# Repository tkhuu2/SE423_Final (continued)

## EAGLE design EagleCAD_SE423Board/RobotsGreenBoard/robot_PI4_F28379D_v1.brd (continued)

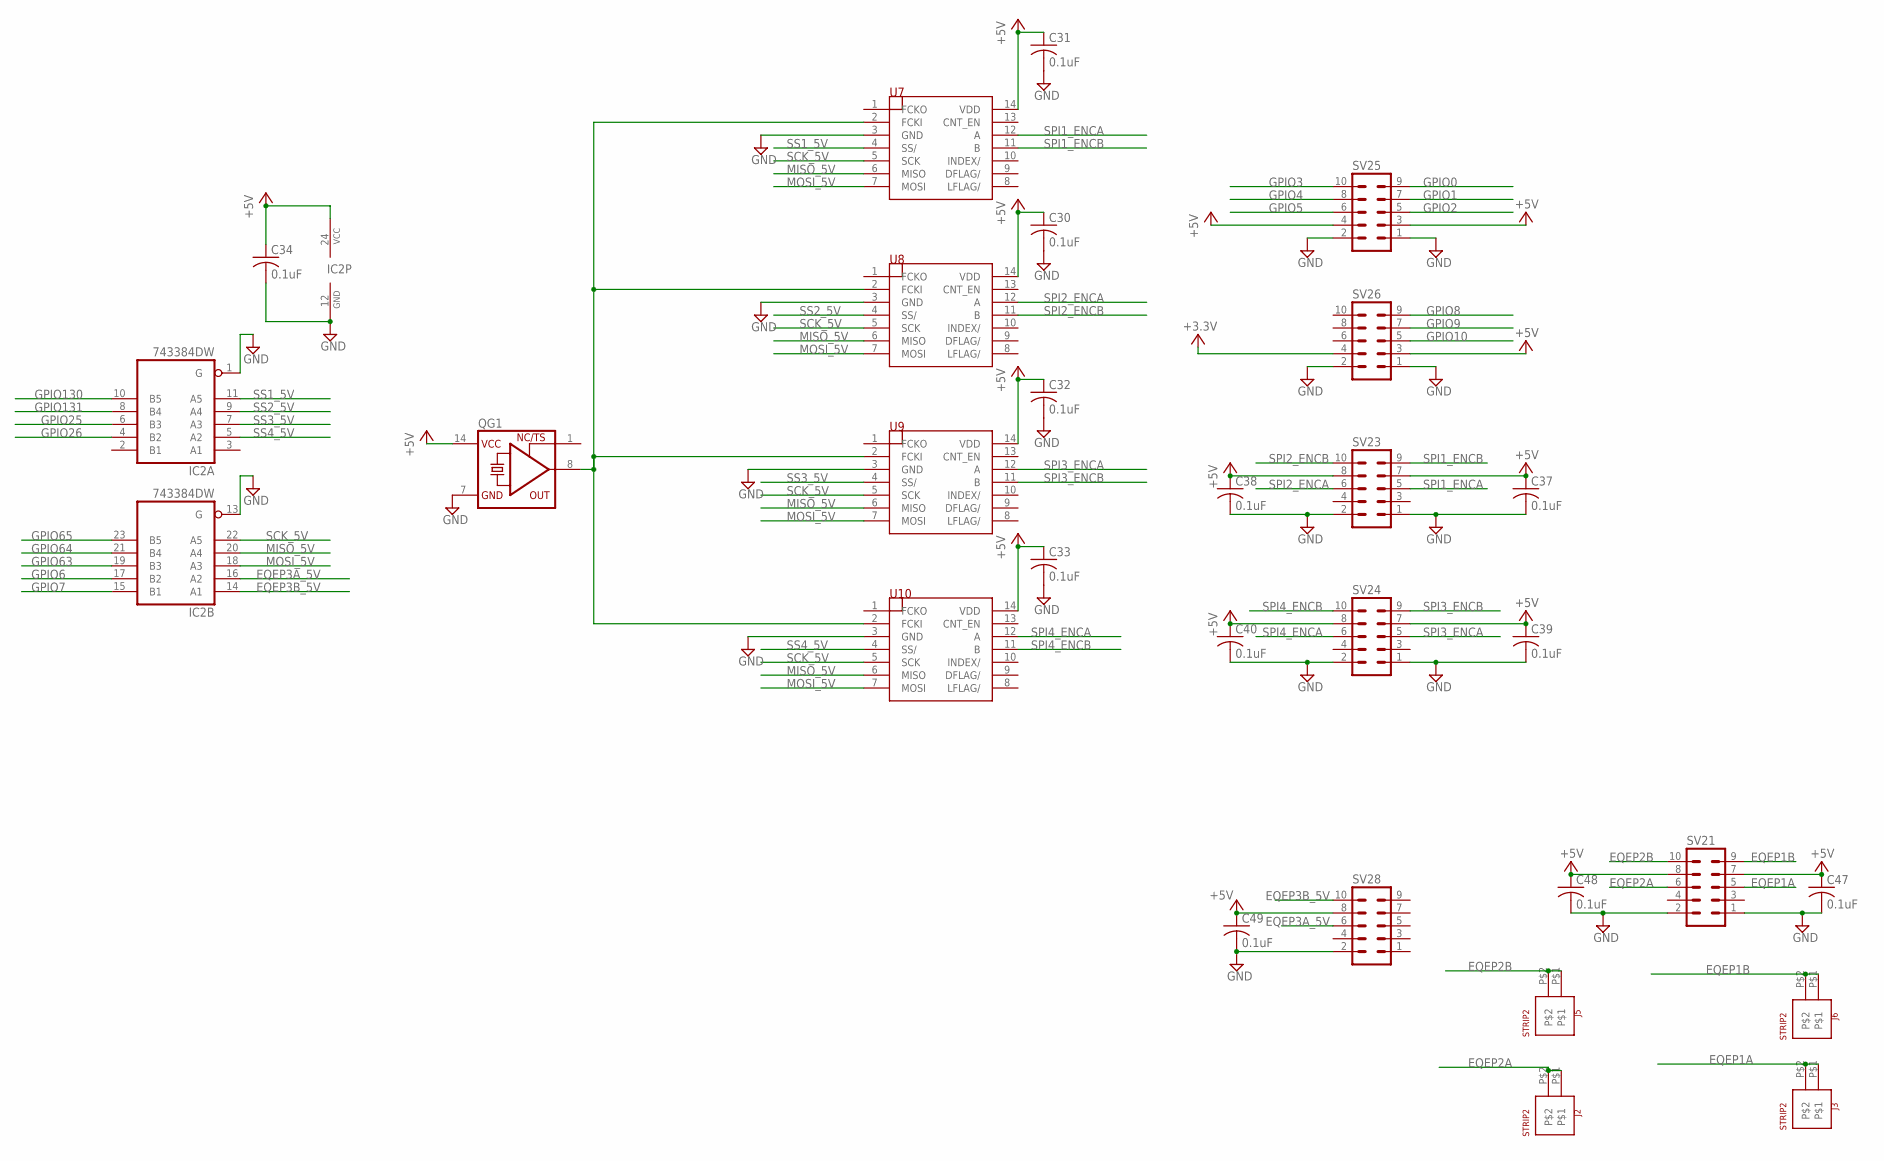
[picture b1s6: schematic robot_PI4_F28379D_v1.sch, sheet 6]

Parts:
C30, C31, C32, C33, C34, C37, C38, C39, C40, C47, C48, C49: 0.1uF; C1206
IC2: 743384DW; SO24W
J2, J3, J5, J6: STRIP2
QG1: XO-14; DIL14S
SV21, SV23, SV24, SV25, SV26, SV28: MA05-2
U7, U8, U9, U10: LS7366R; SO14

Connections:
+3.3V: SV26.4; also elsewhere on the board
+5V: C30.1, C31.1, C32.1, C33.1, C34.1, C37.1, C38.1, C39.1, C40.1, C47.1, C48.1, C49.1, IC2.24 (VCC), QG1.14 (VCC), SV21.7, SV21.8, SV23.7, SV23.8, SV24.7, SV24.8, SV25.3, SV25.4, SV26.3, SV28.8, U7.14 (VDD), U8.14 (VDD), U9.14 (VDD), U10.14 (VDD); also elsewhere on the board
EQEP1A: J3.P$1, J3.P$2, SV21.5
EQEP1B: J6.P$1, J6.P$2, SV21.9
EQEP2A: J2.P$1, J2.P$2, SV21.6
EQEP2B: J5.P$1, J5.P$2, SV21.10
EQEP3A_5V: IC2.16 (A2), SV28.6
EQEP3B_5V: IC2.14 (A1), SV28.10
GND: C30.2, C31.2, C32.2, C33.2, C34.2, C37.2, C38.2, C39.2, C40.2, C47.2, C48.2, C49.2, IC2.1 (G), IC2.12 (GND), IC2.13 (G), QG1.7 (GND), SV21.1, SV21.2, SV23.1, SV23.2, SV24.1, SV24.2, SV25.1, SV25.2, SV26.1, SV26.2, SV28.2, U7.3 (GND), U8.3 (GND), U9.3 (GND), U10.3 (GND); also elsewhere on the board
GPIO0: SV25.9; also elsewhere on the board
GPIO1: SV25.7; also elsewhere on the board
GPIO2: SV25.5; also elsewhere on the board
GPIO3: SV25.10; also elsewhere on the board
GPIO4: SV25.8; also elsewhere on the board
GPIO5: SV25.6; also elsewhere on the board
GPIO6: IC2.17 (B2); also elsewhere on the board
GPIO7: IC2.15 (B1); also elsewhere on the board
GPIO8: SV26.9; also elsewhere on the board
GPIO9: SV26.7; also elsewhere on the board
GPIO10: SV26.5; also elsewhere on the board
GPIO25: IC2.6 (B3); also elsewhere on the board
GPIO26: IC2.4 (B2); also elsewhere on the board
GPIO63: IC2.19 (B3); also elsewhere on the board
GPIO64: IC2.21 (B4); also elsewhere on the board
GPIO65: IC2.23 (B5); also elsewhere on the board
GPIO130: IC2.10 (B5); also elsewhere on the board
GPIO131: IC2.8 (B4); also elsewhere on the board
MISO_5V: IC2.20 (A4), U7.6 (MISO), U8.6 (MISO), U9.6 (MISO), U10.6 (MISO)
MOSI_5V: IC2.18 (A3), U7.7 (MOSI), U8.7 (MOSI), U9.7 (MOSI), U10.7 (MOSI)
unnamed: QG1.8 (OUT), U7.2 (FCKI), U8.2 (FCKI), U9.2 (FCKI), U10.2 (FCKI)
SCK_5V: IC2.22 (A5), U7.5 (SCK), U8.5 (SCK), U9.5 (SCK), U10.5 (SCK)
SPI1_ENCA: SV23.5, U7.12 (A)
SPI1_ENCB: SV23.9, U7.11 (B)
SPI2_ENCA: SV23.6, U8.12 (A)
SPI2_ENCB: SV23.10, U8.11 (B)
SPI3_ENCA: SV24.5, U9.12 (A)
SPI3_ENCB: SV24.9, U9.11 (B)
SPI4_ENCA: SV24.6, U10.12 (A)
SPI4_ENCB: SV24.10, U10.11 (B)
SS1_5V: IC2.11 (A5), U7.4 (SS/)
SS2_5V: IC2.9 (A4), U8.4 (SS/)
SS3_5V: IC2.7 (A3), U9.4 (SS/)
SS4_5V: IC2.5 (A2), U10.4 (SS/)

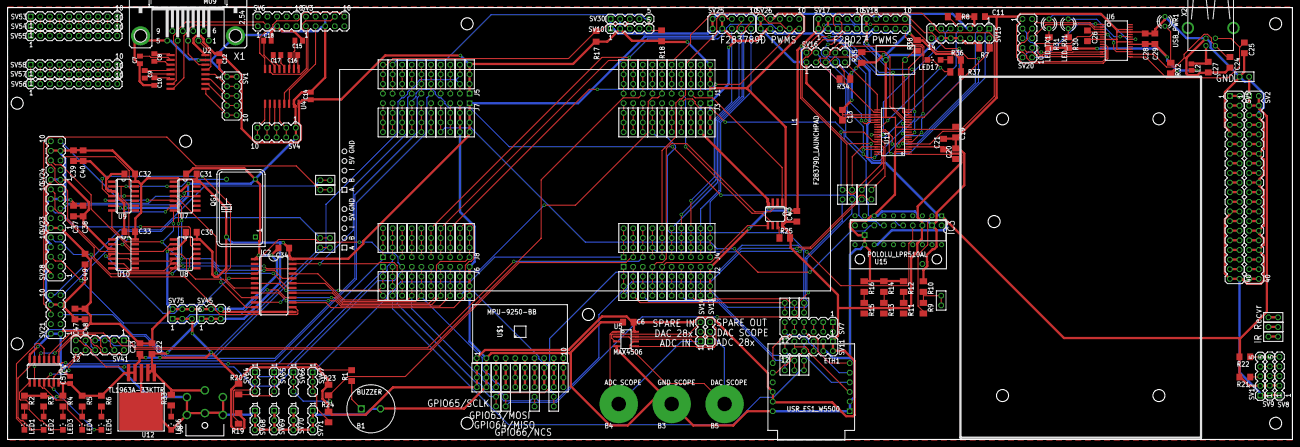
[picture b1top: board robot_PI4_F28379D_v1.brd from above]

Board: 2 copper layers, 339.1 x 114.0 mm, 266 parts (0 on the bottom side), 280 nets.

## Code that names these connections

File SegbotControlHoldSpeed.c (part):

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    // Red LED on LaunchPad
    GPIO_SetupPinMux(34, GPIO_MUX_CPU1, 0);
    GPIO_SetupPinOptions(34, GPIO_OUTPUT, GPIO_PUSHPULL);
    GpioDataRegs.GPBSET.bit.GPIO34 = 1;

    // LED1 and PWM Pin
    GPIO_SetupPinMux(22, GPIO_MUX_CPU1, 0);
    GPIO_SetupPinOptions(22, GPIO_OUTPUT, GPIO_PUSHPULL);
    GpioDataRegs.GPACLEAR.bit.GPIO22 = 1;

    // LED2
    GPIO_SetupPinMux(94, GPIO_MUX_CPU1, 0);
    GPIO_SetupPinOptions(94, GPIO_OUTPUT, GPIO_PUSHPULL);
    GpioDataRegs.GPCCLEAR.bit.GPIO94 = 1;

    // LED3
    GPIO_SetupPinMux(95, GPIO_MUX_CPU1, 0);
    GPIO_SetupPinOptions(95, GPIO_OUTPUT, GPIO_PUSHPULL);
    GpioDataRegs.GPCCLEAR.bit.GPIO95 = 1;

    // LED4
    GPIO_SetupPinMux(97, GPIO_MUX_CPU1, 0);
    GPIO_SetupPinOptions(97, GPIO_OUTPUT, GPIO_PUSHPULL);
    GpioDataRegs.GPDCLEAR.bit.GPIO97 = 1;

    // LED5
    GPIO_SetupPinMux(111, GPIO_MUX_CPU1, 0);
    GPIO_SetupPinOptions(111, GPIO_OUTPUT, GPIO_PUSHPULL);
    GpioDataRegs.GPDCLEAR.bit.GPIO111 = 1;

    // LED6
    GPIO_SetupPinMux(130, GPIO_MUX_CPU1, 0);
    GPIO_SetupPinOptions(130, GPIO_OUTPUT, GPIO_PUSHPULL);
    GpioDataRegs.GPECLEAR.bit.GPIO130 = 1;

    // LED7
    GPIO_SetupPinMux(131, GPIO_MUX_CPU1, 0);
    GPIO_SetupPinOptions(131, GPIO_OUTPUT, GPIO_PUSHPULL);
    GpioDataRegs.GPECLEAR.bit.GPIO131 = 1;

    // LED8
    GPIO_SetupPinMux(25, GPIO_MUX_CPU1, 0);
    GPIO_SetupPinOptions(25, GPIO_OUTPUT, GPIO_PUSHPULL);
    GpioDataRegs.GPACLEAR.bit.GPIO25 = 1;

    // LED9
    GPIO_SetupPinMux(26, GPIO_MUX_CPU1, 0);
    GPIO_SetupPinOptions(26, GPIO_OUTPUT, GPIO_PUSHPULL);
    GpioDataRegs.GPACLEAR.bit.GPIO26 = 1;

    // LED10
    GPIO_SetupPinMux(27, GPIO_MUX_CPU1, 0);
    GPIO_SetupPinOptions(27, GPIO_OUTPUT, GPIO_PUSHPULL);
    GpioDataRegs.GPACLEAR.bit.GPIO27 = 1;

    // LED11
    GPIO_SetupPinMux(60, GPIO_MUX_CPU1, 0);
    GPIO_SetupPinOptions(60, GPIO_OUTPUT, GPIO_PUSHPULL);
    GpioDataRegs.GPBCLEAR.bit.GPIO60 = 1;

    // LED12
    GPIO_SetupPinMux(61, GPIO_MUX_CPU1, 0);
    GPIO_SetupPinOptions(61, GPIO_OUTPUT, GPIO_PUSHPULL);
    GpioDataRegs.GPBCLEAR.bit.GPIO61 = 1;

    // LED13
    GPIO_SetupPinMux(157, GPIO_MUX_CPU1, 0);
    GPIO_SetupPinOptions(157, GPIO_OUTPUT, GPIO_PUSHPULL);
    GpioDataRegs.GPECLEAR.bit.GPIO157 = 1;

    // LED14
    GPIO_SetupPinMux(158, GPIO_MUX_CPU1, 0);
    GPIO_SetupPinOptions(158, GPIO_OUTPUT, GPIO_PUSHPULL);
    GpioDataRegs.GPECLEAR.bit.GPIO158 = 1;

    // LED15
    GPIO_SetupPinMux(159, GPIO_MUX_CPU1, 0);
    GPIO_SetupPinOptions(159, GPIO_OUTPUT, GPIO_PUSHPULL);
    GpioDataRegs.GPECLEAR.bit.GPIO159 = 1;

    // LED16
    GPIO_SetupPinMux(160, GPIO_MUX_CPU1, 0);
    GPIO_SetupPinOptions(160, GPIO_OUTPUT, GPIO_PUSHPULL);
    GpioDataRegs.GPFCLEAR.bit.GPIO160 = 1;

    //WIZNET Reset
    GPIO_SetupPinMux(0, GPIO_MUX_CPU1, 0);
    GPIO_SetupPinOptions(0, GPIO_OUTPUT, GPIO_PUSHPULL);
    GpioDataRegs.GPASET.bit.GPIO0 = 1;

    //ESP8266 Reset
    GPIO_SetupPinMux(1, GPIO_MUX_CPU1, 0);
    GPIO_SetupPinOptions(1, GPIO_OUTPUT, GPIO_PUSHPULL);
    GpioDataRegs.GPASET.bit.GPIO1 = 1;

    //SPIRAM  CS  Chip Select
    GPIO_SetupPinMux(19, GPIO_MUX_CPU1, 0);
    GPIO_SetupPinOptions(19, GPIO_OUTPUT, GPIO_PUSHPULL);
    GpioDataRegs.GPASET.bit.GPIO19 = 1;

    //DRV8874 #1 DIR  Direction
    GPIO_SetupPinMux(29, GPIO_MUX_CPU1, 0);
    GPIO_SetupPinOptions(29, GPIO_OUTPUT, GPIO_PUSHPULL);
    GpioDataRegs.GPASET.bit.GPIO29 = 1;

    //DRV8874 #2 DIR  Direction
    GPIO_SetupPinMux(32, GPIO_MUX_CPU1, 0);
    GPIO_SetupPinOptions(32, GPIO_OUTPUT, GPIO_PUSHPULL);
    GpioDataRegs.GPBSET.bit.GPIO32 = 1;

    //DAN28027  CS  Chip Select
    GPIO_SetupPinMux(9, GPIO_MUX_CPU1, 0);
    GPIO_SetupPinOptions(9, GPIO_OUTPUT, GPIO_PUSHPULL);
    GpioDataRegs.GPASET.bit.GPIO9 = 1;

    //MPU9250  CS  Chip Select
    GPIO_SetupPinMux(66, GPIO_MUX_CPU1, 0);
    GPIO_SetupPinOptions(66, GPIO_OUTPUT, GPIO_PUSHPULL);
    GpioDataRegs.GPCSET.bit.GPIO66 = 1;

    //WIZNET  CS  Chip Select
    GPIO_SetupPinMux(125, GPIO_MUX_CPU1, 0);
    GPIO_SetupPinOptions(125, GPIO_OUTPUT, GPIO_PUSHPULL);
    GpioDataRegs.GPDSET.bit.GPIO125 = 1;

    //Exercise 4, setup GPIO52 as output
    GPIO_SetupPinMux(52, GPIO_MUX_CPU1, 0);
    GPIO_SetupPinOptions(52, GPIO_OUTPUT, GPIO_PUSHPULL);
    GpioDataRegs.GPBSET.bit.GPIO52 = 1;

    //PushButton 1
    GPIO_SetupPinMux(4, GPIO_MUX_CPU1, 0);
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    GPIO_SetupPinMux(15,GPIO_MUX_CPU1,1);

    EALLOW; //ADCA initialization code copied from lab 4
    GpioCtrlRegs.GPAPUD.bit.GPIO14 = 1; // For EPWM8A
    GpioCtrlRegs.GPAPUD.bit.GPIO15 = 1; // For EPWM8B
    EDIS;
    EALLOW;
    //write configurations for all ADCs ADCA, ADCB, ADCC, ADCD
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 //filter out the drum sound, adcb1 interrupt with 51st low pass filter at 200Hz
  __interrupt void ADCB_ISR (void)
 {
  GpioDataRegs.GPBSET.bit.GPIO52 = 1;
  adcb4result = AdcbResultRegs.ADCRESULT0;
  adcb3result = 4095.0 - AdcbResultRegs.ADCRESULT1;
  adcb2result = 4095.0 - AdcbResultRegs.ADCRESULT2;
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  }
  AdcbRegs.ADCINTFLGCLR.bit.ADCINT1 = 1; //clear interrupt flag
  PieCtrlRegs.PIEACK.all = PIEACK_GROUP1;
  GpioDataRegs.GPBCLEAR.bit.GPIO52 = 1;
 }


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    CpuTimer0.InterruptCount++;

    numTimer0calls++;
    //Clear GPIO9 Low to act as a Slave Select. Right now, just to scope. Later to select DAN28027 chip
    //GpioDataRegs.GPACLEAR.bit.GPIO9 = 1; //select dan's chip

    //SpibRegs.SPITXBUF = 0x00DA; // start code for dan's chip
    //SpibRegs.SPITXBUF = 0x4A3B; // 0x4A3B and 0xB517 have no special meaning. Wanted to send
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    }

    // Blink LaunchPad Red LED
    //GpioDataRegs.GPBTOGGLE.bit.GPIO34 = 1;

    // Acknowledge this interrupt to receive more interrupts from group 1
    PieCtrlRegs.PIEACK.all = PIEACK_GROUP1;
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    //dca3result = AdcaResultRegs.ADCRESULT1;
    //a2 = adca2result * 3.0/4095.0;
    //a3 = adca3result * 3.0/4095.0;
    GpioDataRegs.GPCCLEAR.bit.GPIO66 = 1;  //select MPU-9250
    SpibRegs.SPIFFRX.bit.RXFFIL = 8; //Issue the SPIB_RX_INT when 8 values are in the RX FIFO (start address, 3 accel ,readings, a temp reading, 3 gyro readings)
    SpibRegs.SPITXBUF = ((0x8000) | (0x3A00)); //start from register 3A and will be discard
    SpibRegs.SPITXBUF = 0;
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    SpibRegs.SPITXBUF = 0;
    SpibRegs.SPITXBUF = 0;
    SpibRegs.SPITXBUF = 0;
 //   GpioDataRegs.GPCCLEAR.bit.GPIO66 = 1;  //deselect MPU-9250

//    GpioDataRegs.GPBCLEAR.bit.GPIO48 = 1;  //select MyRio-1900
//    SpibRegs.SPIFFRX.bit.RXFFIL = 1; //Issue the SPIB_RX_INT when 1 value are in the RX FIFO (start address, 3 accel ,readings, a temp reading, 3 gyro readings)
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    /*spivalue1 = SpibRegs.SPIRXBUF; // Read first 16 bit value off RX FIFO. Probably is zero since no chip
    spivalue2 = SpibRegs.SPIRXBUF; // Read second 16 bit value off RX FIFO. Again probably zero
    spivalue3 = SpibRegs.SPIRXBUF; // Read third 16 bit value off RX FIFO. Again probably zero */
    GpioDataRegs.GPCSET.bit.GPIO66 = 1; // Set GPIO 9 high to end Slave Select. Now to Scope. Later to deselect DAN28027
    spivalue1 = SpibRegs.SPIRXBUF;  //junk data
    spivalue2 = SpibRegs.SPIRXBUF;  //x accel
    spivalue3 = SpibRegs.SPIRXBUF;  //y accel
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        if(doneCal == 0) {
            GpioDataRegs.GPATOGGLE.bit.GPIO31 = 1; // Blink Blue LED while calibrating
        }
        GpioDataRegs.GPBTOGGLE.bit.GPIO34 = 1; // Always Block Red LED
        UARTPrint = 1; // Tell While loop to print
    }
    SpibRegs.SPIFFRX.bit.RXFFOVFCLR = 1; // Clear Overflow flag just in case of an overflow
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    int16_t temp = 0;
    //Step 1.
    // cut and paste here all the SpibRegs initializations you found for part 3. Make sure the TXdelay in
    //between each transfer to 0. Also dont forget to cut and paste the GPIO settings for GPIO9, 63, 64, 65,
    //66 which are also a part of the SPIB setup.
    SpibRegs.SPIFFCT.bit.TXDLY = 0x00;
    //Exercise 2.1 SPIB setup, now it's inside this function rather than in main()
    GPIO_SetupPinMux(9, GPIO_MUX_CPU1, 0); // Set as GPIO9 and used as DAN28027 SS
    GPIO_SetupPinOptions(9, GPIO_OUTPUT, GPIO_PUSHPULL); // Make GPIO9 an Output Pin
    GpioDataRegs.GPASET.bit.GPIO9 = 1; //Initially Set GPIO9/SS High so DAN28027 is not selected
    GPIO_SetupPinMux(66, GPIO_MUX_CPU1, 0); // Set as GPIO66 and used as MPU-9250 SS
    GPIO_SetupPinOptions(66, GPIO_OUTPUT, GPIO_PUSHPULL); // Make GPIO66 an Output Pin
    GpioDataRegs.GPCSET.bit.GPIO66 = 1; //Initially Set GPIO66/SS High so MPU-9250 is not selected
    GPIO_SetupPinMux(48, GPIO_MUX_CPU1, 0); // Set as GPIO66 and used as MyRio SS
    GPIO_SetupPinOptions(48, GPIO_OUTPUT, GPIO_PUSHPULL); // Make GPIO48 an Output Pin
    GpioDataRegs.GPBSET.bit.GPIO48 = 1; //Initially Set GPIO48/SS High so MyRio is not selected
    GPIO_SetupPinMux(63, GPIO_MUX_CPU1, 15); //Set GPIO63 pin to SPISIMOB
    GPIO_SetupPinMux(64, GPIO_MUX_CPU1, 15); //Set GPIO64 pin to SPISOMIB
    GPIO_SetupPinMux(65, GPIO_MUX_CPU1, 15); //Set GPIO65 pin to SPICLKB
    EALLOW;
    GpioCtrlRegs.GPBPUD.bit.GPIO63 = 0; // Enable Pull-ups on SPI PINs Recommended by TI for SPI Pins
    GpioCtrlRegs.GPCPUD.bit.GPIO64 = 0;
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
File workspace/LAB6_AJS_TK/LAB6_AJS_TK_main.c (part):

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float adcc3VOLT = 0.0; //voltage from ADCINC3 AJS
float adcc4VOLT = 0.0; //voltage from ADCINC4 AJS
float adcc5VOLT = 0.0; //voltage from ADCINC5 AJS
uint16_t adcc2result = 0; //raw 12 bit data from ADCINC2 AJS
uint16_t adcc3result = 0; //raw 12 bit data from ADCINC3 AJS
uint16_t adcc4result = 0; //raw 12 bit data from ADCINC4 AJS
uint16_t adcc5result = 0; //raw 12 bit data from ADCINC5 AJS
float fineZ = 0.0; //deg/s for 4Z AJS
float fineX = 0.0; //deg/s for 4X AJS
float roughZ = 0.0; //deg/s for Z AJS
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    // Red LED on LaunchPad
    GPIO_SetupPinMux(34, GPIO_MUX_CPU1, 0);
    GPIO_SetupPinOptions(34, GPIO_OUTPUT, GPIO_PUSHPULL);
    GpioDataRegs.GPBSET.bit.GPIO34 = 1;

    // LED1 and PWM Pin
    GPIO_SetupPinMux(22, GPIO_MUX_CPU1, 0);
    GPIO_SetupPinOptions(22, GPIO_OUTPUT, GPIO_PUSHPULL);
    GpioDataRegs.GPACLEAR.bit.GPIO22 = 1;

    // LED2
    GPIO_SetupPinMux(94, GPIO_MUX_CPU1, 0);
    GPIO_SetupPinOptions(94, GPIO_OUTPUT, GPIO_PUSHPULL);
    GpioDataRegs.GPCCLEAR.bit.GPIO94 = 1;

    // LED3
    GPIO_SetupPinMux(95, GPIO_MUX_CPU1, 0);
    GPIO_SetupPinOptions(95, GPIO_OUTPUT, GPIO_PUSHPULL);
    GpioDataRegs.GPCCLEAR.bit.GPIO95 = 1;

    // LED4
    GPIO_SetupPinMux(97, GPIO_MUX_CPU1, 0);
    GPIO_SetupPinOptions(97, GPIO_OUTPUT, GPIO_PUSHPULL);
    GpioDataRegs.GPDCLEAR.bit.GPIO97 = 1;

    // LED5
    GPIO_SetupPinMux(111, GPIO_MUX_CPU1, 0);
    GPIO_SetupPinOptions(111, GPIO_OUTPUT, GPIO_PUSHPULL);
    GpioDataRegs.GPDCLEAR.bit.GPIO111 = 1;

    // LS7366#1 CS
    GPIO_SetupPinMux(130, GPIO_MUX_CPU1, 0);
    GPIO_SetupPinOptions(130, GPIO_OUTPUT, GPIO_PUSHPULL);
    GpioDataRegs.GPECLEAR.bit.GPIO130 = 1;

    // LS7366#2 CS
    GPIO_SetupPinMux(131, GPIO_MUX_CPU1, 0);
    GPIO_SetupPinOptions(131, GPIO_OUTPUT, GPIO_PUSHPULL);
    GpioDataRegs.GPECLEAR.bit.GPIO131 = 1;

    // LS7366#3 CS
    GPIO_SetupPinMux(25, GPIO_MUX_CPU1, 0);
    GPIO_SetupPinOptions(25, GPIO_OUTPUT, GPIO_PUSHPULL);
    GpioDataRegs.GPACLEAR.bit.GPIO25 = 1;

    // LS7366#4 CS
    GPIO_SetupPinMux(26, GPIO_MUX_CPU1, 0);
    GPIO_SetupPinOptions(26, GPIO_OUTPUT, GPIO_PUSHPULL);
    GpioDataRegs.GPACLEAR.bit.GPIO26 = 1;

    // WIZNET RST
    GPIO_SetupPinMux(27, GPIO_MUX_CPU1, 0);
    GPIO_SetupPinOptions(27, GPIO_OUTPUT, GPIO_PUSHPULL);
    GpioDataRegs.GPACLEAR.bit.GPIO27 = 1;

    //PushButton 1
    GPIO_SetupPinMux(157, GPIO_MUX_CPU1, 0);
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    //SPIRAM  CS  Chip Select
    GPIO_SetupPinMux(19, GPIO_MUX_CPU1, 0);
    GPIO_SetupPinOptions(19, GPIO_OUTPUT, GPIO_PUSHPULL);
    GpioDataRegs.GPASET.bit.GPIO19 = 1;

    //F28027 CS
    GPIO_SetupPinMux(29, GPIO_MUX_CPU1, 0);
    GPIO_SetupPinOptions(29, GPIO_OUTPUT, GPIO_PUSHPULL);
    GpioDataRegs.GPASET.bit.GPIO29 = 1;

    //MPU9250  CS  Chip Select
    GPIO_SetupPinMux(66, GPIO_MUX_CPU1, 0);
    GPIO_SetupPinOptions(66, GPIO_OUTPUT, GPIO_PUSHPULL);
    GpioDataRegs.GPCSET.bit.GPIO66 = 1;

    //WIZNET  CS  Chip Select
    GPIO_SetupPinMux(125, GPIO_MUX_CPU1, 0);
    GPIO_SetupPinOptions(125, GPIO_OUTPUT, GPIO_PUSHPULL);
    GpioDataRegs.GPDSET.bit.GPIO125 = 1;

    GPIO_SetupPinMux(61, GPIO_MUX_CPU1, 0);
    GPIO_SetupPinOptions(61, GPIO_OUTPUT, GPIO_PUSHPULL);
    GpioDataRegs.GPBCLEAR.bit.GPIO61 = 1;

    GPIO_SetupPinMux(67, GPIO_MUX_CPU1, 0);
    GPIO_SetupPinOptions(67, GPIO_OUTPUT, GPIO_PUSHPULL);
    GpioDataRegs.GPCCLEAR.bit.GPIO67 = 1;

    GPIO_SetupPinMux(0, GPIO_MUX_CPU1, 1);  //Set GPIO0s pin function to EPWM1A    TK
    GPIO_SetupPinMux(2, GPIO_MUX_CPU1, 1); //Set GPIO2s pin function to EPWM2A.    TK

    // Clear all interrupts and initialize PIE vector table:
    // Disable CPU interrupts
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    init_eQEPs();

    EALLOW;
    GpioCtrlRegs.GPAPUD.bit.GPIO0 = 1;  // For EPWM1A   TK
    GpioCtrlRegs.GPAPUD.bit.GPIO2 = 1;  // For EPWM2A   TK
    EDIS;

    EALLOW;
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
    if ((numTimer0calls%5) == 0) {
        // Blink LaunchPad Red LED
        GpioDataRegs.GPBTOGGLE.bit.GPIO34 = 1;
    }

    // Acknowledge this interrupt to receive more interrupts from group 1
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    adcc4VOLT = adcc4result * (3.0/4095.0); //fine Z AJS
    adcc5VOLT = adcc5result * (3.0/4095.0); //rough Z AJS
    //----------------------SPIB START TRANSMISSION----------------------------------//
    GpioDataRegs.GPCCLEAR.bit.GPIO66 = 1; //slave select low AJS
    SpibRegs.SPIFFRX.bit.RXFFIL = 8; // Interrupt at 8 values in FIFO AJS
    //Send garbage to required addresses in order to receive data in SPIB interrupt AJS
    SpibRegs.SPITXBUF = (0x8000 | 0x3A00); //Start at address 58 (INT_STATUS) for write and RX discard AJS
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
__interrupt void SPIB_isr(void){
    int16_t trash = 0;
    GpioDataRegs.GPCSET.bit.GPIO66 = 1; // Set GPIO 66 high to end Slave Select. Now to Scope. Later to deselect MPU9250.

    /*spivalue1 = SpibRegs.SPIRXBUF; // Read first 16 bit value off RX FIFO. Probably is zero since no chip
    spivalue2 = SpibRegs.SPIRXBUF; // Read second 16 bit value off RX FIFO. Again probably zero
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    int16_t trash = 0;
    //Step 1.
    // cut and paste here all the SpibRegs initializations you found for part 3. Also dont forget to cut and
    //paste the GPIO settings for GPIO9, 63, 64, 65, 66 which are also a part of the SPIB setup.
    //-----------------------------------------------------------------------------------------------------------------
    //SPI settings AJS
    GPIO_SetupPinMux(66, GPIO_MUX_CPU1, 0); // Set as GPIO66 and used as MPU-9250 SS
    GPIO_SetupPinOptions(66, GPIO_OUTPUT, GPIO_PUSHPULL); // Make GPIO66 an Output Pin
    GpioDataRegs.GPCSET.bit.GPIO66 = 1; //Initially Set GPIO66/SS High so MPU-9250 is not selected
    GPIO_SetupPinMux(63, GPIO_MUX_CPU1, 15); //Set GPIO63 pin to SPISIMOB
    GPIO_SetupPinMux(64, GPIO_MUX_CPU1, 15); //Set GPIO64 pin to SPISOMIB
    GPIO_SetupPinMux(65, GPIO_MUX_CPU1, 15); //Set GPIO65 pin to SPICLKB
    EALLOW;
    GpioCtrlRegs.GPBPUD.bit.GPIO63 = 0; // Enable Pull-ups on SPI PINs Recommended by TI for SPI Pins
    GpioCtrlRegs.GPCPUD.bit.GPIO64 = 0;
    GpioCtrlRegs.GPCPUD.bit.GPIO65 = 0;
    GpioCtrlRegs.GPBQSEL2.bit.GPIO63 = 3; // Set I/O pin to asynchronous mode recommended for SPI
    GpioCtrlRegs.GPCQSEL1.bit.GPIO64 = 3; // Set I/O pin to asynchronous mode recommended for SPI
    GpioCtrlRegs.GPCQSEL1.bit.GPIO65 = 3; // Set I/O pin to asynchronous mode recommended for SPI
    EDIS;
    // ---------------------------------------------------------------------------
    SpibRegs.SPICCR.bit.SPISWRESET = 0; // Put SPI in Reset
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    // perform a multiple 16 bit transfer to initialize MPU-9250 registers 0x13,0x14,0x15,0x16
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    // some code is given, most you have to fill you yourself.
    GpioDataRegs.GPCCLEAR.bit.GPIO66 = 1; // Slave Select Low

    // Perform the number of needed writes to SPITXBUF to write to all 13 registers. Remember we are
    //sending 16 bit transfers, so two registers at a time after the first 16 bit transfer.
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
    // wait for the correct number of 16 bit values to be received into the RX FIFO
    while(SpibRegs.SPIFFRX.bit.RXFFST != 7);
    GpioDataRegs.GPCSET.bit.GPIO66 = 1; // Slave Select High
    //Clear RX buffer AJS
    trash = SpibRegs.SPIRXBUF;
    trash = SpibRegs.SPIRXBUF;
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    // perform a multiple 16 bit transfer to initialize MPU-9250 registers 0x23,0x24,0x25,0x26
    // 0x27, 0x28, 0x29. Use only one SS low to high for all these writes
    // some code is given, most you have to fill you yourself.
    GpioDataRegs.GPCCLEAR.bit.GPIO66 = 1; // Slave Select Low

    // Perform the number of needed writes to SPITXBUF to write to all 7 registers
    // To address 00x23 write 0x00 FIFO EN
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
    // wait for the correct number of 16 bit values to be received into the RX FIFO
    while(SpibRegs.SPIFFRX.bit.RXFFST != 4);
    GpioDataRegs.GPCSET.bit.GPIO66 = 1; // Slave Select High
    //Clear RX buffer AJS
    trash = SpibRegs.SPIRXBUF;
    trash = SpibRegs.SPIRXBUF;
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
    //Step 4.
    // perform a single 16 bit transfer to initialize MPU-9250 register 0x2A
    GpioDataRegs.GPCCLEAR.bit.GPIO66 = 1;
    // Write to address 0x2A the value 0x81 I2C SLV1 CTRL
    SpibRegs.SPITXBUF = 0x2A81;
    // wait for one byte to be received
    while(SpibRegs.SPIFFRX.bit.RXFFST != 1);
    GpioDataRegs.GPCSET.bit.GPIO66 = 1;
    trash = SpibRegs.SPIRXBUF;
    DELAY_US(10);

    // The Remainder of this code is given to you.
    GpioDataRegs.GPCCLEAR.bit.GPIO66 = 1;

    SpibRegs.SPITXBUF = (0x3800 | 0x0001); // 0x3800 INT ENABLE
    while(SpibRegs.SPIFFRX.bit.RXFFST !=1);
    GpioDataRegs.GPCSET.bit.GPIO66 = 1;
    trash = SpibRegs.SPIRXBUF;
    DELAY_US(10);
    GpioDataRegs.GPCCLEAR.bit.GPIO66 = 1;

    SpibRegs.SPITXBUF = (0x3A00 | 0x0001); // 0x3A00 INT STATUS
    while(SpibRegs.SPIFFRX.bit.RXFFST !=1);
    GpioDataRegs.GPCSET.bit.GPIO66 = 1;
    trash = SpibRegs.SPIRXBUF;
    DELAY_US(10);
    GpioDataRegs.GPCCLEAR.bit.GPIO66 = 1;

    SpibRegs.SPITXBUF = (0x6400 | 0x0001); // 0x6400 I2C SLV1 DO
    while(SpibRegs.SPIFFRX.bit.RXFFST !=1);
    GpioDataRegs.GPCSET.bit.GPIO66 = 1;
    trash = SpibRegs.SPIRXBUF;
    DELAY_US(10);
    GpioDataRegs.GPCCLEAR.bit.GPIO66 = 1;
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
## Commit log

2022-09-21 add f28027 fft starter
2022-09-26 test post build step
2022-09-26 add post compile step to lab starter
2022-10-03 update cmd file for c2prog ffttf in page 0 flash
2022-10-04 Changed .projectspec for Labstarter and SPIRAMstarter to use C 2011
2022-10-04 Modified labstarter_f2807 so it uses C 2011 version
2023-01-02 Added HWStarter and Modified LABstarter need to test code
2023-01-02 Added LADAR_PICOM_starter, FinalProjectStarter, and AstarProjectStarter
2023-01-05 Made sure baud rate to RPI4 is 2083332
2023-01-09 added F2833x device, could possibly be uses for a project
2023-01-09 added ls7366 code to f2802x device
2023-01-10 Added CANstarter Need to test
2023-01-11 Fix Comments in HW and Lab starter
2023-01-11 Added --c11 to CANstarter build
2023-01-11 Updated some comments to different source files
2023-01-16 Type O in FinalProjectStarter fixed
2023-01-16 Added XINTstarter project
2023-01-16 Added fftstarter and fftDMAstarter projects
2023-01-16 Added CLAstarter and SWI3starter
2023-01-16 Added ESP8266starter
2023-01-18 change readme
2023-01-18 Added Robot EagleCAD schematic
2023-01-19 Added F28027Board Schematic
2023-01-23 Added Linux starter code
2023-01-28 committed LADAR SCIP2 version of LADAR
2023-01-28 modify the linux file for getting lidar SCIP2.0 data
2023-02-06 Added Raspberry Pi 4's bcm2711 Peripheral DataSheet
2023-03-13 added OpenMV files
2023-03-13 added LadarSerialApp_shm_plot
2023-03-13 Changed serial_COMandOpti.c for Yixiao Kernel 2083333
2023-03-15 Added change in print text for serialCOMandOpti and C2Prog starter project
2023-03-23 Small change to CANstarter_main.c
2023-04-11 added gripper parts
2023-04-12 inserted lab 6
2023-04-12 Exercise 1
2023-04-12 done for the day
2023-04-12 message
2023-04-19 exercise 4 is done lab 7
2023-04-19 lab 7 done
2023-04-29 worked on obstacle avoidance and gripper doors
2023-04-30 commented cases
2023-04-30 astar updates 30APR23
2023-04-30 last astar updates
2023-05-01 1-MAY: A* LADAR stuff
2023-05-02 Dan updates
2023-05-02 bug algoithm
2023-05-05 astar diagonal update
2023-05-05 userxy comments
2023-05-06 drop off stuff works
2023-05-07 started working on updating map
2023-05-12 dis hoe done
